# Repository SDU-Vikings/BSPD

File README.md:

# BSPD
Formula Student -- Brake System Plausibility Device

# Brake System Plausibility Device 

Formula Student  
Ruleset: FS-Rules_2018_V1.1  
This BSPD passed scrutineering at Formula Student UK 2018  
Please let us know if you used this design for your car or if you have used it and made useful improvements to it  
Also if you have any questions please let us know --> [SDU-Vikings](https://www.facebook.com/SDUVikings/?hc_ref=ARTjX442SZMKwcmNnhHa4KYyQpRgB5dD4x-7G2Z0j-hZw_FMgdILzyK0XDBPWNJGz00)

## Schematic and PCB

The project is made in KiCad. Get it here --> [KiCad 5.0](http://kicad-pcb.org/download/)  
The schematic layout and PCB layout is found in the ``KiCad/`` subfolder.

## Components

The design is made for a battery supply of between 11 V and 15 V.   
The current consumption is measured at between 63,0 and 90,3 mA with a 12,7 V supply.

For current measurement [LEM HAS 100-S](https://export.rsdelivers.com/product/lem/has-100s/lem-has-series-open-loop-current-sensor-300a/3019495) is used. The Hall Effect Sensor needs +-15 V supply hence the [TEN 8-1223](https://export.rsdelivers.com/product/tracopower/ten-8-1223/tracopower-ten-8-8w-isolated-dc-dc-converter/4239628).  
For brake presssure measurement [EPT3100](https://www.variohm.com/images/datasheets/EPT3100_Pressure_Sensor_1608_T.pdf) is used.  
The relay for the safety chain is [TE-OJ-SS-112LMH2](https://export.rsdelivers.com/product/te-connectivity/oj-ss-112lmh2005/te-connectivity-spno-non-latching-relay-pcb-mount/6802518).

### Debugging LED's

The design includes SMD-sized LED's for easier debugging. **D3** and **D4** can be removed altogether and **D6** replaced by an ordinary P/N-diode.

### Delay-block

[LTC6994](https://export.rsdelivers.com/product/linear-technology/ltc6994is6-1trmpbf/linear-technology-ltc6994is6-1trmpbf-programmable/8580894) is as delay-block. The delay-block is configured for a delay of 500 ms. See [LTC6994 One Shot](http://beta-tools.analog.com/timerblox/LTC6994) to configure delay and use ``LTC6994.json`` for the setup.

### Latch and latch-reset

The signal from the delay-block is received by a latch [CD4043B](https://export.rsdelivers.com/product/texas-instruments/cd4043bd/texas-instruments-cd4043bd-quad-latch-transparent/6607616) that will latch on to the signal requiring power cycling of the low voltage system to reset it again.  
However the latch will latch on to a high signal when the low voltage system is turned on initially. The 555-circuit is used for generating a pulse, that will reset the latch. The pulse has a delay of approximately 500 ms at turn on. 

## Input signals and voltage dividers

### Current

HAS_100-S has a output voltage range of -12V to +12V with a voltage signal of 4 V for every 100 A in the wire.   
With a nominal battery voltage of 510,6 V the current to the motors at 9,8 A is below 5 kW as required by EV7.5.5 in the rules.  
```math
510,6 \,\mathrm{V} \cdot 9,7 \,\mathrm{A} \approx 4.953 \,\mathrm{W} 
```

At this current in the HV-wires the voltage output from the hall effect sensor is 0,388 V.  
The voltage divider between **R6** and **R11+R12||R13** gives a voltage treshold of 0,380, which corresponds to a current of 9,5 A in the wires.

```math
\frac{2600}{100000 + 2600} \cdot 15\, \mathrm{V} \approx 0,380\, \mathrm{V}
```

Change the value of **R6**, **R11**, **R12** and **R13** to adjust the voltage treshold of the comparator.

### Brake

Change the value of **R27** and **R33** to adjust the voltage treshold of the comparator for the brake pressure sensor.

## Current Measurement

The design includes operational amplifiers whose purpose is to convert the voltage range of the hall effect sensor signal from (-12V/+12V) to (0V/10V) for interfacing with a controller.  
It is not required for the intended functionality of the BSPD and can be removed.

**U10B** is a summation operational amplifier. The gain on the current sensor output is -5/24. This is summed to a voltage of -2,5 V converting the voltage range to (-5 V/0V). **U10A** has a gain of -2 converting the voltage range to the desired (0V/10V). **U11A** is a buffer.

## Labels in the schematic

``DCDC+``           +15 V  
``DCDC-``           -15 V  
``BSPD_TEST``       - Signal from controller to simulate 5 kW drawn from the battery pack  
``BSPD_STATUS``     - Signal to controller to show BSPD status. High when there is a BSPD fault  
``SC_IN``           - Safety chain in  
``SC_OUT``          - Safety chain out  
``Latch_Reset``     - From 555-timer-circuit. Used to pulse reset the latch   
``Current_Sensor``  - Voltage signal from LEM HAS 100-S  
``Brake_Sensor``    - Voltage signal from EPT3100  
``Analog_GND``      - Supplied GND to EPT3100. This is shorted to GND at the controller  
``Analog_5V``       - 5 V supplied to EPT3100

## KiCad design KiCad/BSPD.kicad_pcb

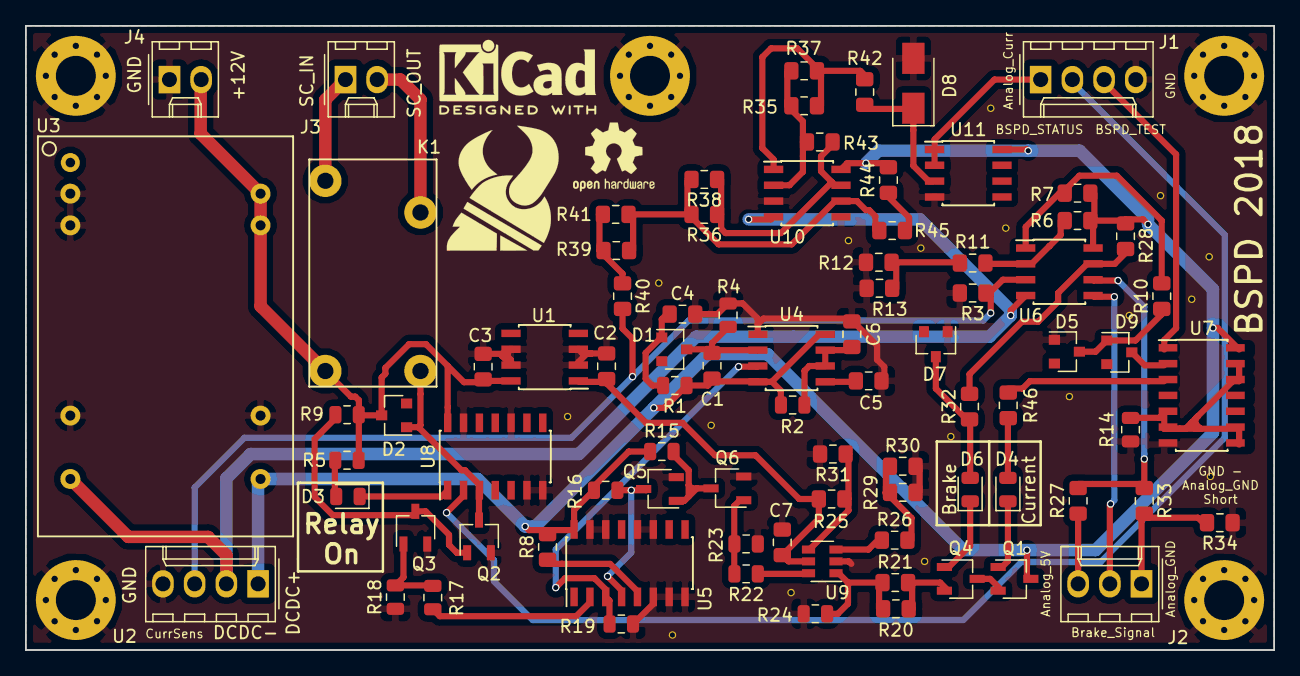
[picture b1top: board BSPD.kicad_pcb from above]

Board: 2 copper layers, 100.0 x 50.0 mm, 84 parts (0 on the bottom side), 56 nets.

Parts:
C1: 1µ; C_0805_2012Metric_Pad1.15x1.40mm_HandSolder
C2, C7: 0,1 µF; C_0805_2012Metric_Pad1.15x1.40mm_HandSolder
C3: 0,33 µF; C_0805_2012Metric_Pad1.15x1.40mm_HandSolder
C4, C6: 4,7µ; C_0805_2012Metric_Pad1.15x1.40mm_HandSolder
C5: 100n; C_0805_2012Metric_Pad1.15x1.40mm_HandSolder
D1, D2, D5, D7, D9: BAS16LT1; D_SOT-23_ANK
D3, D4, D6: LED; D_0805_2012Metric
D8: 10V; D_SMA
J1: Conn_01x04; Molex_KK-254_AE-6410-04A_1x04_P2.54mm_Vertical
J2: Conn_01x03; Molex_KK-254_AE-6410-03A_1x03_P2.54mm_Vertical
J3, J4: Conn_01x02; Molex_KK-254_AE-6410-02A_1x02_P2.54mm_Vertical
K1: TE-OJ-SS-112LMH2; TE-OJ-Series_Miniature-PCB-Relay
Q1, Q4: MMBT3904; TSOT-23
Q2, Q3, Q5, Q6: 2N7002; TSOT-23
R1, R2, R4, R5, R9, R14, R15, R16, R18, R19, R23: 10k; R_0805_2012Metric
R3, R6: 100k; R_0805_2012Metric_Pad1.15x1.40mm_HandSolder
R7, R8, R10, R27, R28, R32, R33, R36, R38, R42, R43, R46: 10k; R_0805_2012Metric_Pad1.15x1.40mm_HandSolder
R11, R13, R41: 2,2k; R_0805_2012Metric_Pad1.15x1.40mm_HandSolder
R12: 220; R_0805_2012Metric_Pad1.15x1.40mm_HandSolder
R17, R22: 33; R_0805_2012Metric
R20, R21: 3,3k; R_0805_2012Metric_Pad1.15x1.40mm_HandSolder
R24: 680; R_0805_2012Metric
R25: 1M; R_0805_2012Metric_Pad1.15x1.40mm_HandSolder
R26: 68k; R_0805_2012Metric_Pad1.15x1.40mm_HandSolder
R29: 33k; R_0805_2012Metric_Pad1.15x1.40mm_HandSolder
R30: 150k; R_0805_2012Metric_Pad1.15x1.40mm_HandSolder
R31: 680k; R_0805_2012Metric_Pad1.15x1.40mm_HandSolder
R34: 0; R_0805_2012Metric_Pad1.15x1.40mm_HandSolder
R35: 220k; R_0805_2012Metric_Pad1.15x1.40mm_HandSolder
R37, R39, R40: 22k; R_0805_2012Metric_Pad1.15x1.40mm_HandSolder
R44, R45: 15k; R_0805_2012Metric_Pad1.15x1.40mm_HandSolder
U1: L78L05_SO8; SOIC-8_3.9x4.9mm_P1.27mm
U2: HAS_100-S; Molex_KK-254_AE-6410-04A_1x04_P2.54mm_Vertical
U3: TEN8-1223
U4: LM555; SOIC-8_3.9x4.9mm_P1.27mm
U5: CD4043B; SOIC-16_3.9x9.9mm_P1.27mm
U6: LM2903; SOIC-8_3.9x4.9mm_P1.27mm
U7: HEF4071; SOIC-14_3.9x8.7mm_P1.27mm
U8: CD4041UB; SOIC-14_3.9x8.7mm_P1.27mm
U9: LTC6994; SOT-23-6
U10, U11: TL072; SOIC-8_3.9x4.9mm_P1.27mm

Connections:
+5V: C2.1, C7.1, R25.1, U1.1, U9.5
+12V: C3.1, D2.1, J4.2, K1.1, R5.1, R9.1, U1.8, U3.22, U3.23, U8.14
/Sheet5B6518BB/Analog_HV_Current_Measurement: J1.1, U11.1, U11.2
Analog_5v: J2.3, R27.1
Analog_GND: J2.1, R33.2, R34.2
BSPD_STATUS: J1.2, U8.2
BSPD_TEST: J1.3, U7.1
Brake_Signal: J2.2, U6.5
Current_Sensor_Out: R3.1, R40.2, U2.3, U6.3
DCDC+: C1.1, Q1.3, R1.1, R2.1, R6.1, R7.1, R8.2, R15.1, R16.1, R28.1, R44.2, U2.1, U3.14, U4.4, U4.8, U5.16, U6.8, U7.14, U10.8, U11.8
DCDC-: U2.2, U3.11, U6.4, U10.4
GND: C2.2, C3.2, C4.2, C5.2, C6.2, C7.2, D5.2, D7.2, D8.2, J1.4, J4.1, Q2.2, Q3.2, Q5.2, Q6.2, R3.2, R4.2, R12.2, R13.2, R14.2, R18.1, R19.1, R23.1, R24.1, R29.2, R30.2, R31.2, R34.1, U1.2, U1.3, U1.6, U1.7, U2.4, U3.2, U3.3, U3.9, U3.16, U4.1, U5.6, U5.7, U5.8, U5.11, U5.12, U5.14, U5.15, U7.7, U8.6, U8.7, U8.10, U8.13, U9.2, U10.3, U10.5, U11.4
Latch_Reset: R19.2, U4.3, U5.3
unnamed: C1.2, D1.1, R4.1, U4.2
unnamed: C4.1, D1.2, R1.2
unnamed: C5.1, U4.5
unnamed: C6.1, R2.2, U4.6, U4.7
unnamed: D2.2, K1.2, Q2.3, U8.3
unnamed: D3.1, U8.1
unnamed: D3.2, R5.2
unnamed: D4.1, Q1.1
unnamed: D4.2, R46.1
unnamed: D5.1, D9.2, R10.1
unnamed: D6.1, Q4.1
unnamed: D6.2, D7.1, R32.1
unnamed: D8.1, R42.2, U11.3
unnamed: D9.1, U7.2
unnamed: Q1.2, Q4.3
unnamed: Q2.1, Q3.3, R9.2
unnamed: Q3.1, R17.2, R18.2
unnamed: Q4.2, R20.2, R21.2
unnamed: Q5.1, Q6.3, R15.2
unnamed: Q5.3, R16.2, U5.4
unnamed: Q6.1, R22.2, R23.2
unnamed: R8.1, U5.5
unnamed: R7.2, R10.2, U6.1
unnamed: R6.2, R11.1, U6.2
unnamed: R11.2, R12.1, R13.1
unnamed: R14.1, U7.5, U7.6, U7.8, U7.9, U7.12, U7.13
unnamed: R17.1, U5.2
unnamed: R20.1, R21.1, R24.2, U9.1
unnamed: R22.1, U9.6
unnamed: R25.2, R31.1, U9.4
unnamed: R26.1, U9.3
unnamed: R26.2, R29.1, R30.1
unnamed: R27.2, R33.1, U6.6
unnamed: R28.2, R32.2, U6.7
unnamed: R35.1, R37.1, R42.1, U10.1
unnamed: R35.2, R37.2, R43.1, U10.2
unnamed: R36.1, R38.1, R43.2, U10.7
unnamed: R36.2, R38.2, R39.1, R41.1, R45.1, U10.6
unnamed: R39.2, R40.1, R41.2
unnamed: R44.1, R45.2
unnamed: R46.2, U7.3
SC_IN: J3.1, K1.4
SC_OUT: J3.2, K1.3

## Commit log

2018-08-23 Create newfolder
2018-08-23 Update KiCad
2018-08-23 Create rescue-backup
2018-08-23 Update rescue-backup
